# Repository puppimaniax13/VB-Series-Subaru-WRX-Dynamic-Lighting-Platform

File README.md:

# 2022+ Subaru WRX Dynamic LED Reflector Platform

A full-stack hardware and software solution to replace static OEM rear reflectors with addressable, reactive LED modules. This project features a modular PCB designed for the VB chassis but adaptable to any 12V automotive lighting application.

## 🚀 Technical Overview
- **Mechanical:** Custom 3D-printed housings (Fusion 360) designed for OEM fitment.
- **Electrical:** Dual-layer custom PCB (KiCad) with 12V->5V buck regulation and signal filtering.
- **Software:** C++ Firmware (Arduino) utilizing **FastLED** for sequential animations and interrupt-driven brake logic.

## 🛠️ Hardware Stack
- **MCU:** ESP-32-S3-WROOM
- **LEDs:** WS2812B Addressable Strips
- **Design Tools:** KiCad 9.0, Autodesk Fusion 360, Adobe Lightroom (Documentation)
- **3D Printer:** Bambu Labs P1S, PLA & PETG

## 📂 Repository Structure
- `/Firmware`: Arduino source code (.ino)
- `/Hardware`: KiCad project files & PCB Schematics
- `/Mechanical`: .3mf files for printing
- `/Media`: High-res project photography

## 🖨️ 3D Printing
- When using the provided *.3mf* files please try not to adjust much.
- The filament used for the lens is as follows
  - Overture Transparent PETG
  - Bambu Translucent Grey PETG
  - Overture Transparent Red PETG

## ⚖️ License
Code/Firmware: This project is licensed under the **GNU GPLv3**. You are free to use and modify it, but any derivative works must also be open-sourced under the same license.

Hardware & Design (PCB/3D Models): Licensed under CC BY-NC-SA 4.0. Personal use is encouraged; commercial use or resale of these designs is strictly prohibited without prior authorization.

*Commercial use or resale of these designs is strictly prohibited.*

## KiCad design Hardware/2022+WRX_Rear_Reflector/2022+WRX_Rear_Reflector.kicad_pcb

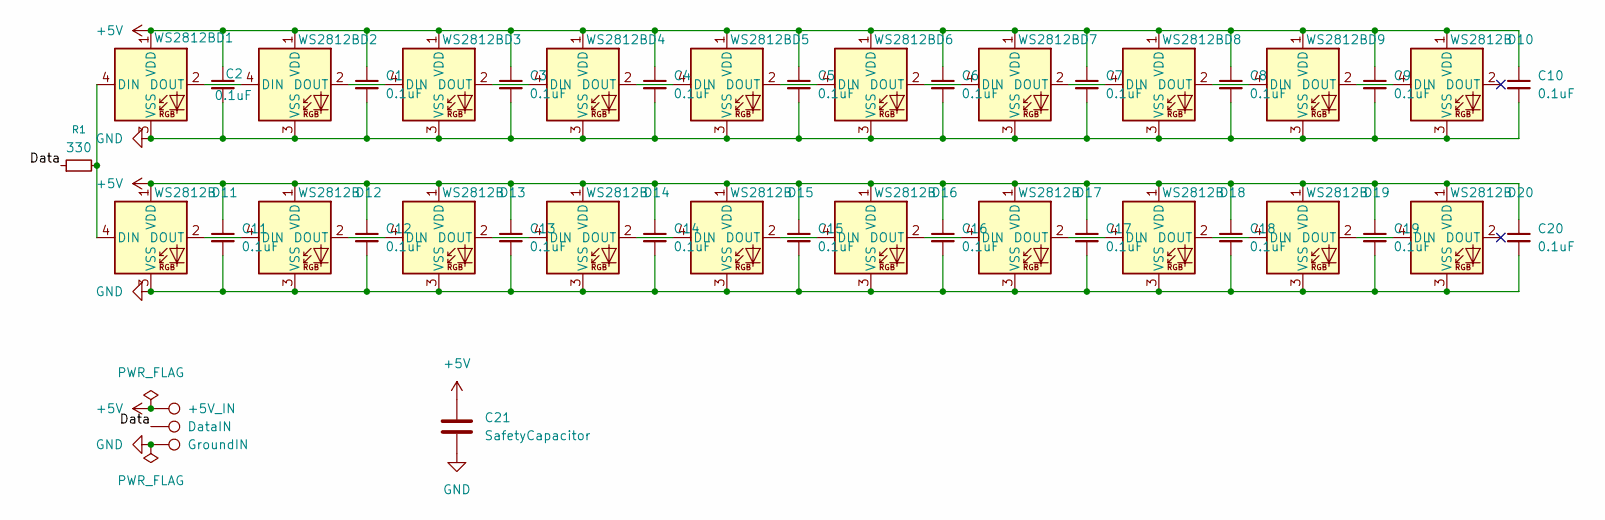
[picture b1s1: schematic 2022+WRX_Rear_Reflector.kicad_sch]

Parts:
C1, C2, C3, C4, C5, C6, C7, C8, C9, C10, C11, C12, C13, C14, C15, C16, C17, C18, C19, C20: 0.1uF; C_0504_1310Metric
C21: SafetyCapacitor; C_1206_3216Metric
D1, D2, D3, D4, D5, D6, D7, D8, D9, D10, D11, D12, D13, D14, D15, D16, D17, D18, D19, D20: WS2812B; LED_WS2812B_PLCC4_5.0x5.0mm_P3.2mm
R1: 330; R_0603_1608Metric
TP1: GroundIN; TestPoint_THTPad_D1.5mm_Drill0.7mm
TP2: DataIN; TestPoint_THTPad_D1.5mm_Drill0.7mm
TP3: +5V_IN; TestPoint_THTPad_D1.5mm_Drill0.7mm

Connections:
+5V: C1.1, C2.1, C3.1, C4.1, C5.1, C6.1, C7.1, C8.1, C9.1, C10.1, C11.1, C12.1, C13.1, C14.1, C15.1, C16.1, C17.1, C18.1, C19.1, C20.1, C21.1, D1.1 (VDD), D2.1 (VDD), D3.1 (VDD), D4.1 (VDD), D5.1 (VDD), D6.1 (VDD), D7.1 (VDD), D8.1 (VDD), D9.1 (VDD), D10.1 (VDD), D11.1 (VDD), D12.1 (VDD), D13.1 (VDD), D14.1 (VDD), D15.1 (VDD), D16.1 (VDD), D17.1 (VDD), D18.1 (VDD), D19.1 (VDD), D20.1 (VDD), TP3.1; also elsewhere on the board
/Data: R1.1, TP2.1; also elsewhere on the board
GND: C1.2, C2.2, C3.2, C4.2, C5.2, C6.2, C7.2, C8.2, C9.2, C10.2, C11.2, C12.2, C13.2, C14.2, C15.2, C16.2, C17.2, C18.2, C19.2, C20.2, C21.2, D1.3 (VSS), D2.3 (VSS), D3.3 (VSS), D4.3 (VSS), D5.3 (VSS), D6.3 (VSS), D7.3 (VSS), D8.3 (VSS), D9.3 (VSS), D10.3 (VSS), D11.3 (VSS), D12.3 (VSS), D13.3 (VSS), D14.3 (VSS), D15.3 (VSS), D16.3 (VSS), D17.3 (VSS), D18.3 (VSS), D19.3 (VSS), D20.3 (VSS), TP1.1; also elsewhere on the board
unnamed: D1.4 (DIN), D11.4 (DIN), R1.2
unnamed: D1.2 (DOUT), D2.4 (DIN)
unnamed: D2.2 (DOUT), D3.4 (DIN)
unnamed: D3.2 (DOUT), D4.4 (DIN)
unnamed: D4.2 (DOUT), D5.4 (DIN)
unnamed: D5.2 (DOUT), D6.4 (DIN)
unnamed: D6.2 (DOUT), D7.4 (DIN)
unnamed: D7.2 (DOUT), D8.4 (DIN)
unnamed: D8.2 (DOUT), D9.4 (DIN)
unnamed: D9.2 (DOUT), D10.4 (DIN)
unnamed: D11.2 (DOUT), D12.4 (DIN)
unnamed: D12.2 (DOUT), D13.4 (DIN)
unnamed: D13.2 (DOUT), D14.4 (DIN)
unnamed: D14.2 (DOUT), D15.4 (DIN)
unnamed: D15.2 (DOUT), D16.4 (DIN)
unnamed: D16.2 (DOUT), D17.4 (DIN)
unnamed: D17.2 (DOUT), D18.4 (DIN)
unnamed: D18.2 (DOUT), D19.4 (DIN)
unnamed: D19.2 (DOUT), D20.4 (DIN)

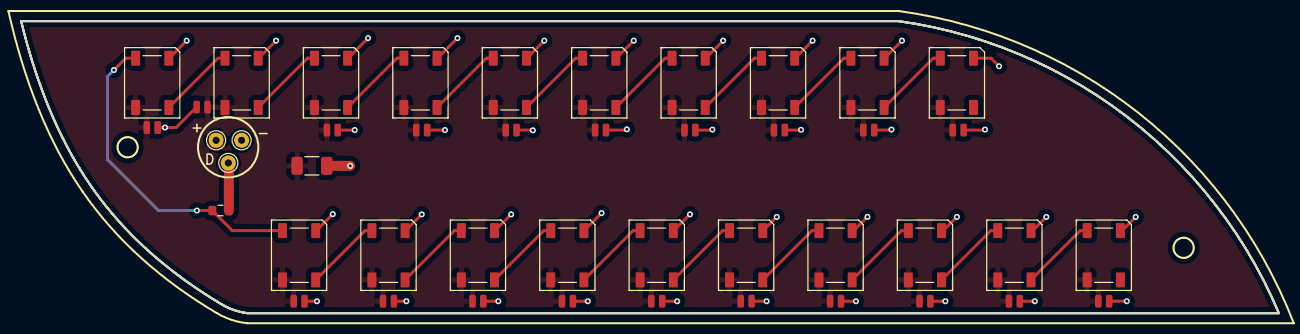
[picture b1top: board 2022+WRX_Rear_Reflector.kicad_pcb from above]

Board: 2 copper layers, 125.1 x 29.0 mm, 45 parts (0 on the bottom side), 22 nets.

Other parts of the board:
+: +5V_IN; TestPoint_THTPad_D1.5mm_Drill0.7mm
-: GroundIN; TestPoint_THTPad_D1.5mm_Drill0.7mm
D: DataIN; TestPoint_THTPad_D1.5mm_Drill0.7mm

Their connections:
+5V: +.1; also elsewhere on the board
/Data: D.1; also elsewhere on the board
GND: -.1; also elsewhere on the board

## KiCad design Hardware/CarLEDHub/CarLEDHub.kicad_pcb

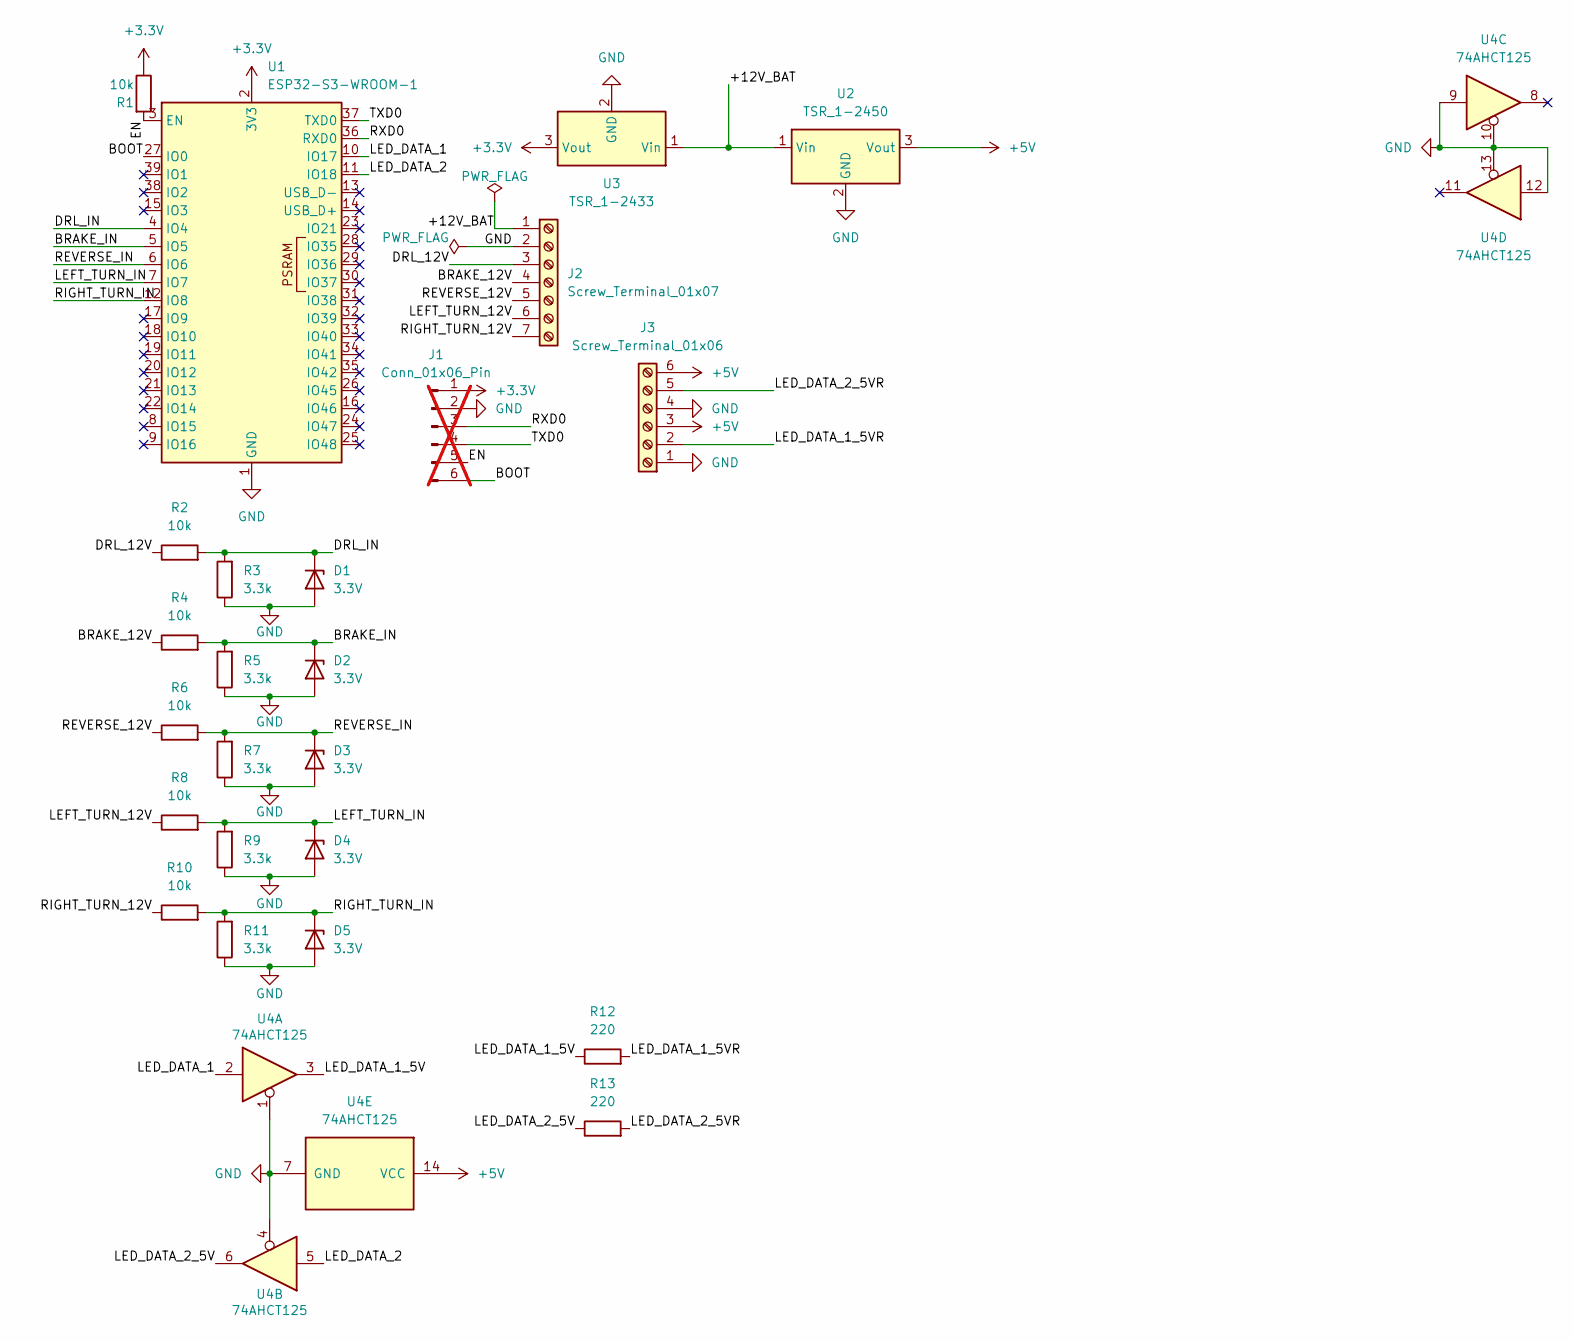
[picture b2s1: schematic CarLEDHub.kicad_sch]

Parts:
D1, D2, D3, D4, D5: 3.3V; D_SOD-123; LCSC C173413
J1: Conn_01x06_Pin; PinHeader_1x06_P2.54mm_Vertical; not fitted
J2: Screw_Terminal_01x07; TerminalBlock_Phoenix_MKDS-1,5-7_1x07_P5.00mm_Horizontal
J3: Screw_Terminal_01x06; TerminalBlock_Phoenix_MKDS-1,5-6_1x06_P5.00mm_Horizontal
R1, R2, R4, R6, R8, R10: 10k; R_0805_2012Metric
R3, R5, R7, R9, R11: 3.3k; R_0805_2012Metric
R12, R13: 220; R_0805_2012Metric
U1: ESP32-S3-WROOM-1; LCSC C2913576
U2: TSR_1-2450; Converter_DCDC_TRACO_TSR-1_THT; LCSC C5346721
U3: TSR_1-2433; Converter_DCDC_TRACO_TSR-1_THT; LCSC C5189115
U4: 74AHCT125; SOIC-14_3.9x8.7mm_P1.27mm

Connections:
+3.3V: J1.1, R1.1, U1.2 (3V3), U3.3 (Vout); also elsewhere on the board
+5V: J3.3, J3.6, U2.3 (Vout), U4.14 (VCC)
/+12V_BAT: J2.1, U2.1 (Vin), U3.1 (Vin)
/BOOT: J1.6, U1.27 (IO0); also elsewhere on the board
/BRAKE_12V: J2.4, R4.1
/BRAKE_IN: D2.1 (K), R4.2, R5.2, U1.5 (IO5)
/DRL_12V: J2.3, R2.1
/DRL_IN: D1.1 (K), R2.2, R3.2, U1.4 (IO4)
/EN: J1.5, R1.2, U1.3 (EN); also elsewhere on the board
/LED_DATA_1: U1.10 (IO17), U4.2
/LED_DATA_1_5V: R12.1, U4.3
/LED_DATA_1_5VR: J3.2, R12.2
/LED_DATA_2: U1.11 (IO18), U4.5
/LED_DATA_2_5V: R13.1, U4.6
/LED_DATA_2_5VR: J3.5, R13.2
/LEFT_TURN_12V: J2.6, R8.1
/LEFT_TURN_IN: D4.1 (K), R8.2, R9.2, U1.7 (IO7)
/REVERSE_12V: J2.5, R6.1
/REVERSE_IN: D3.1 (K), R6.2, R7.2, U1.6 (IO6)
/RIGHT_TURN_12V: J2.7, R10.1
/RIGHT_TURN_IN: D5.1 (K), R10.2, R11.2, U1.12 (IO8)
/RXD0: J1.3, U1.36 (RXD0); also elsewhere on the board
/TXD0: J1.4, U1.37 (TXD0); also elsewhere on the board
GND: D1.2 (A), D2.2 (A), D3.2 (A), D4.2 (A), D5.2 (A), J1.2, J2.2, J3.1, J3.4, R3.1, R5.1, R7.1, R9.1, R11.1, U1.1 (GND), U1.40 (GND), U1.41 (GND), U2.2 (GND), U3.2 (GND), U4.1, U4.4, U4.7 (GND), U4.9, U4.10, U4.12, U4.13; also elsewhere on the board

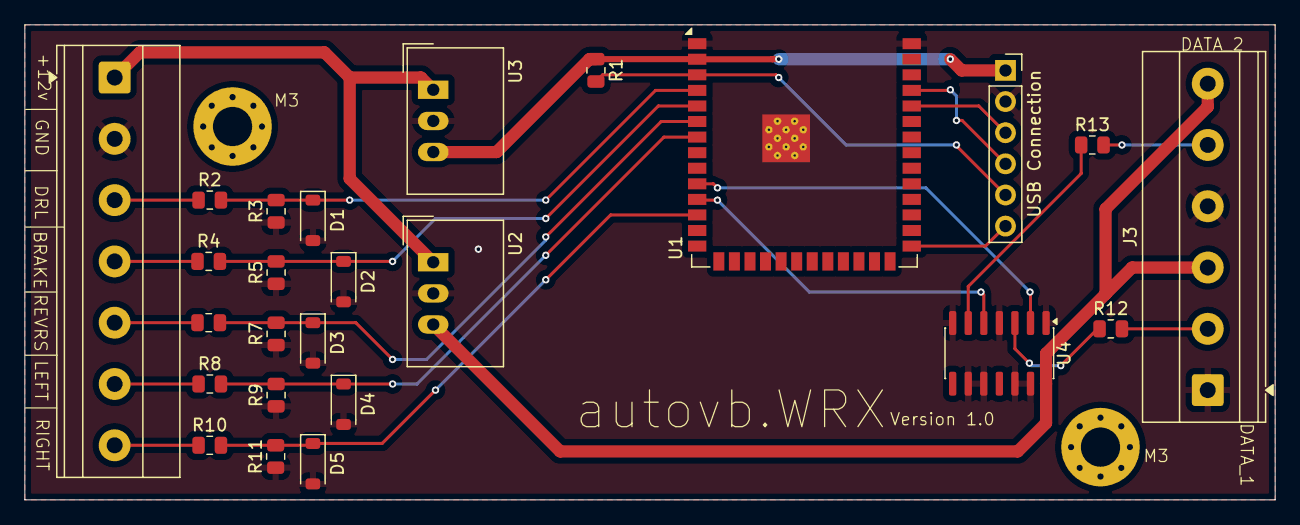
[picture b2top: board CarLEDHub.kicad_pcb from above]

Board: 2 copper layers, 102.0 x 38.7 mm, 25 parts (0 on the bottom side), 24 nets.

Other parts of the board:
USB Connection: Conn_01x06_Pin; PinSocket_1x06_P2.54mm_Vertical

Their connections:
+3.3V: USB Connection.1; also elsewhere on the board
/BOOT: USB Connection.6; also elsewhere on the board
/EN: USB Connection.5; also elsewhere on the board
/RXD0: USB Connection.3; also elsewhere on the board
/TXD0: USB Connection.4; also elsewhere on the board
GND: USB Connection.2; also elsewhere on the board

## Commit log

2026-02-26 Add KiCad for Hub
    LEDHub that is the brains of the operation.
2026-02-26 Added Rear Reflector PCB (WIP)
    WORK IN PROGRESS
2026-02-28 Update AuraCore v1.3
    Added "tuner" settings to modify and fine tune, as well as an HTML preview for local viewing.
2026-03-01 Update AuraCore v1.4
    Added the ability to set how many LED's and brought back the sleep times.
2026-03-24 AuraCore.ino v2
    Reworked the design with the help of Claude.ai. Still have more changes to come in the design.
